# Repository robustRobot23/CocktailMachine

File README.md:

# CocktailMachine
Check the project Wiki for more information
Currently working on a cocktail machine to pour a shot of liquor, and pump in up to 4 mixers.
Machine contains:
  - 1 Stepper motor
  - 1 A4998 Stepper driver
  - 4 12V DC diagrpham pumps
  - 1 24 LED Neopixel ring
  - 1 Loadcell and HX711 breakout board
  - PCB V1
  - 1 OLED Screen
  - 2 rotary encoder dials and pushbuttons
  
**Code still not fully to working.** 
Currently creating the code structure:
  Machine class
  Cocktail class
  Pump Class

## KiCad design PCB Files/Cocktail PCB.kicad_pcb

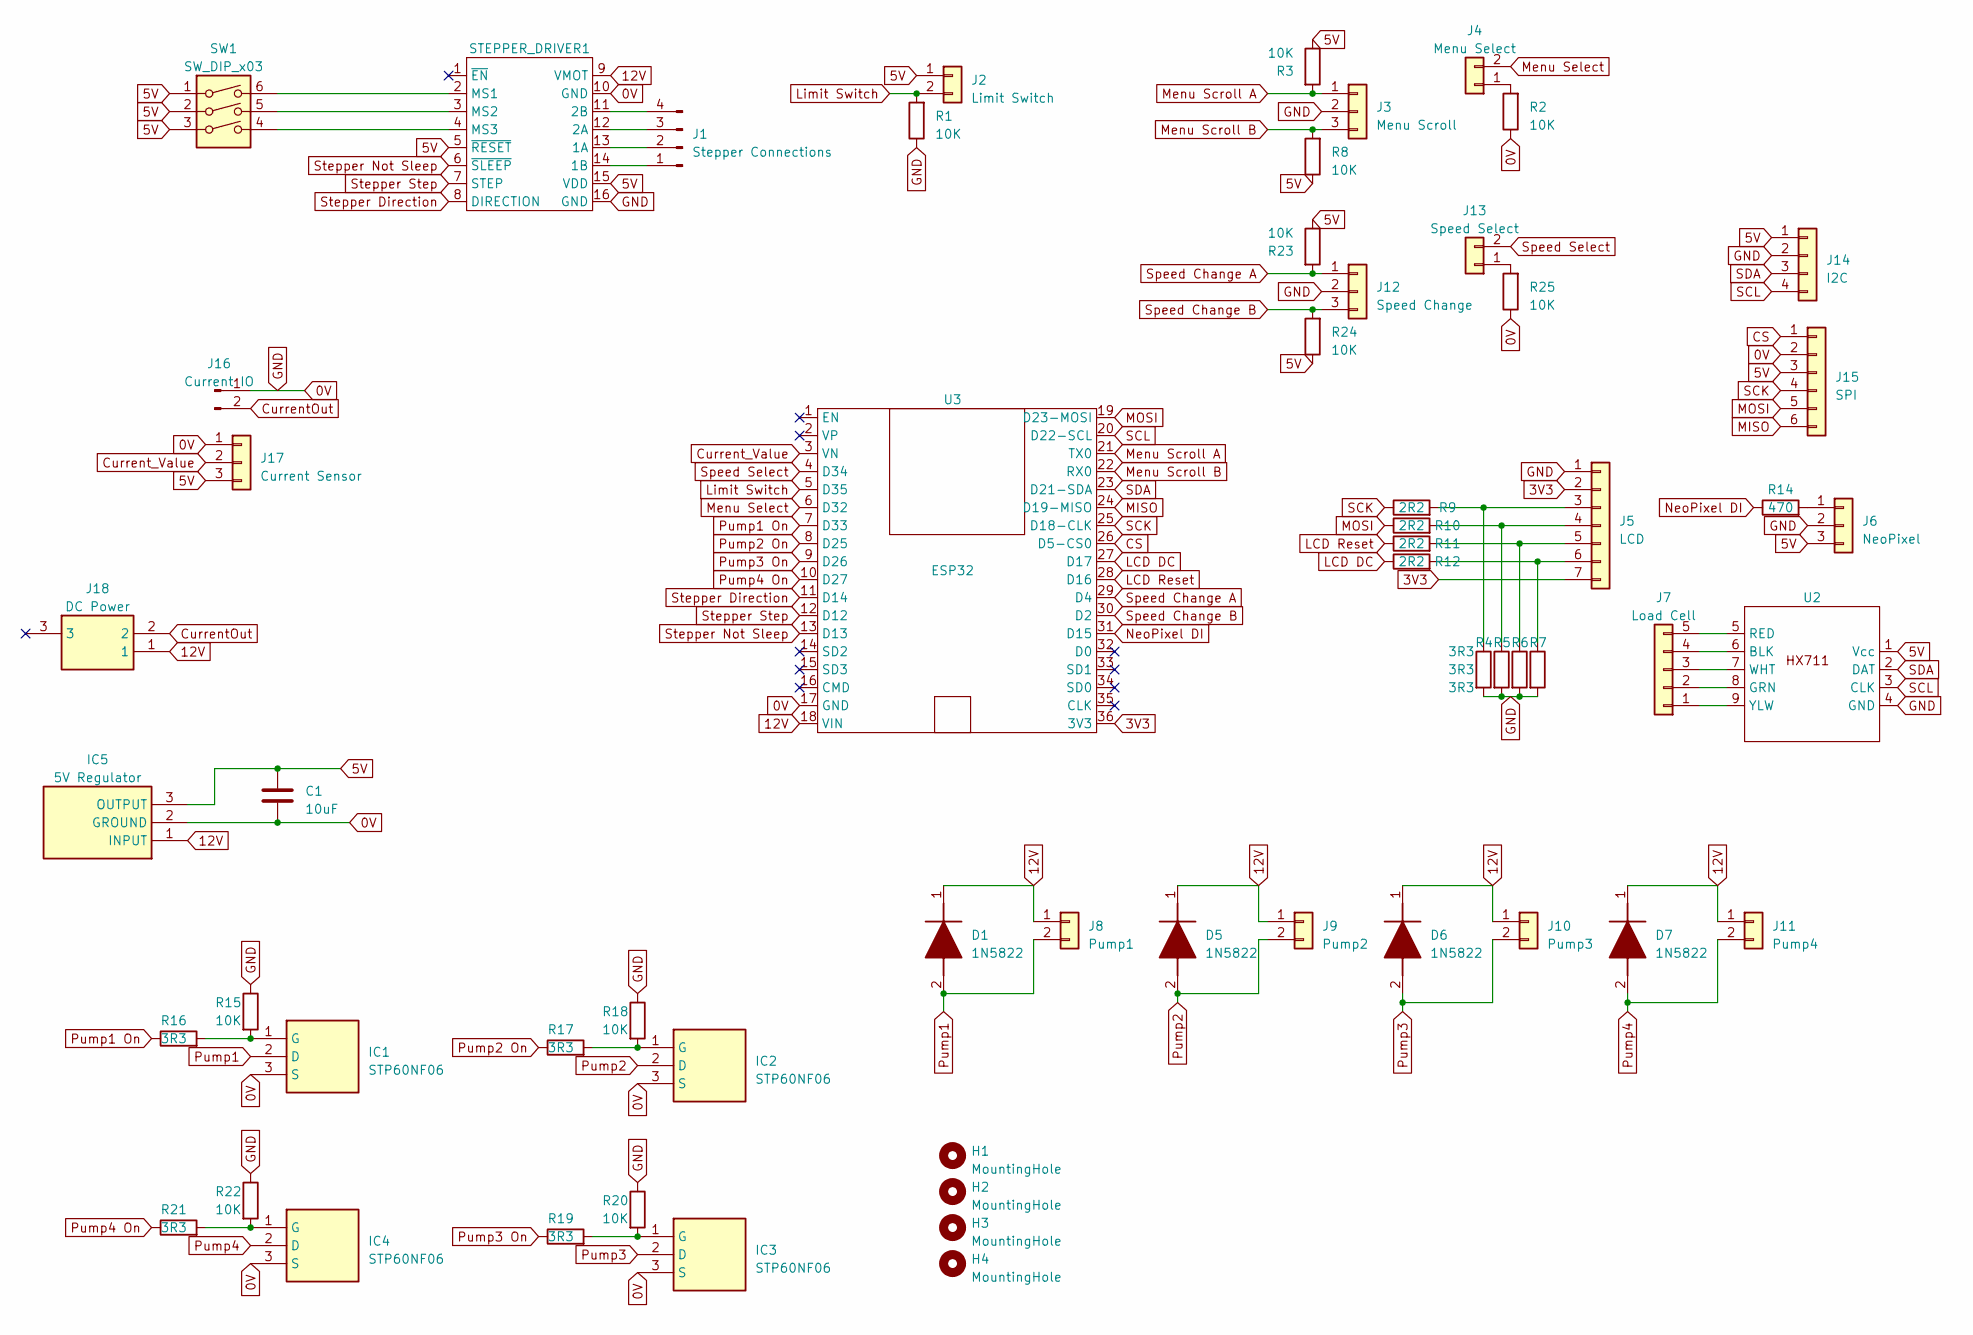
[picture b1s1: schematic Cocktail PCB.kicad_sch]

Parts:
C1: 10uF; CP_Radial_D5.0mm_P2.50mm
D1, D5, D6, D7: 1N5822; D_DO-41_SOD81_P10.16mm_Horizontal; Manufacturer_Part_Number 1N5822; Mouser Part Number 512-1N5822
H1, H2, H3, H4: MountingHole; MountingHole_3.5mm_Pad
IC1, IC2, IC3, IC4: STP60NF06; TO270P460X1020X2008-3P; Manufacturer_Part_Number STP60NF06; Mouser Part Number 511-STP60NF06
IC5: 5V Regulator; TO270P460X1020X2008-3P; Manufacturer_Part_Number LM340T-5.0; Mouser Part Number 926-LM340T-50
J1: Stepper Connections; PinHeader_1x04_P2.54mm_Vertical
J2: Limit Switch; PinHeader_1x02_P2.54mm_Vertical
J3: Menu Scroll; PinHeader_1x03_P2.54mm_Vertical
J4: Menu Select; PinHeader_1x02_P2.54mm_Vertical
J5: LCD; PinHeader_1x07_P2.54mm_Vertical
J6: NeoPixel; PinHeader_1x03_P2.54mm_Vertical
J7: Load Cell; PinHeader_1x05_P2.54mm_Vertical
J8: Pump1; PinHeader_1x02_P2.54mm_Vertical
J9: Pump2; PinHeader_1x02_P2.54mm_Vertical
J10: Pump3; PinHeader_1x02_P2.54mm_Vertical
J11: Pump4; PinHeader_1x02_P2.54mm_Vertical
J12: Speed Change; PinHeader_1x03_P2.54mm_Vertical
J13: Speed Select; PinHeader_1x02_P2.54mm_Vertical
J14: I2C; PinHeader_1x04_P2.54mm_Vertical
J15: SPI; PinHeader_1x06_P2.54mm_Vertical
J16: Current IO; PinHeader_1x02_P2.54mm_Vertical
J17: Current Sensor; PinHeader_1x03_P2.54mm_Vertical
J18: DC Power; DC Jack; Manufacturer_Part_Number PJ-102AH
R1, R2, R3, R8, R15, R18, R20, R22, R23, R24, R25: 10K; R_0805_2012Metric_Pad1.20x1.40mm_HandSolder
R4, R5, R6, R7, R16, R17, R19, R21: 3R3; R_0805_2012Metric_Pad1.20x1.40mm_HandSolder
R9, R10, R11, R12: 2R2; R_0805_2012Metric_Pad1.20x1.40mm_HandSolder
R14: 470; R_0805_2012Metric_Pad1.20x1.40mm_HandSolder
STEPPER_DRIVER1: A4988
SW1: SW_DIP_x03; DIL Switch
U2: HX711
U3: ESP32; DOIT ESP32 DEVKIT

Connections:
0V: C1.2, IC1.3 (S), IC2.3 (S), IC3.3 (S), IC4.3 (S), IC5.2 (GROUND), J3.2, J5.1, J6.2, J12.2, J14.2, J15.2, J16.1, J17.1, R1.1, R2.1, R4.2, R5.2, R6.2, R7.2, R15.1, R18.1, R20.1, R22.1, R25.1, STEPPER_DRIVER1.10 (GND), STEPPER_DRIVER1.16 (GND), U2.4 (GND), U3.17 (GND)
3V3: J5.2, J5.7, U3.36 (3V3)
5V: C1.1, IC5.3 (OUTPUT), J2.1, J6.3, J14.1, J15.3, J17.3, R3.1, R8.1, R23.1, R24.1, STEPPER_DRIVER1.5 (~RESET), STEPPER_DRIVER1.15 (VDD), SW1.1, SW1.2, SW1.3, U2.1 (Vcc)
12V: D1.1 (K), D5.1 (K), D6.1 (K), D7.1 (K), IC5.1 (INPUT), J8.1, J9.1, J10.1, J11.1, J18.1, STEPPER_DRIVER1.9 (VMOT), U3.18 (VIN)
CS: J15.1, U3.26 (D5-CS0)
CurrentOut: J16.2, J18.2
Current_Value: J17.2, U3.3 (VN)
LCD DC: R12.1, U3.27 (D17)
LCD Reset: R11.1, U3.28 (D16)
Limit Switch: J2.2, R1.2, U3.5 (D35)
MISO: J15.6, U3.24 (D19-MISO)
MOSI: J15.5, R10.1, U3.19 (D23-MOSI)
Menu Scroll A: J3.1, R3.2, U3.21 (TX0)
Menu Scroll B: J3.3, R8.2, U3.22 (RX0)
Menu Select: J4.2, U3.6 (D32)
NeoPixel DI: R14.1, U3.31 (D15)
unnamed: IC1.1 (G), R15.2, R16.2
unnamed: IC2.1 (G), R17.2, R18.2
unnamed: IC3.1 (G), R19.2, R20.2
unnamed: IC4.1 (G), R21.2, R22.2
unnamed: J1.1, STEPPER_DRIVER1.14 (1B)
unnamed: J1.2, STEPPER_DRIVER1.13 (1A)
unnamed: J1.3, STEPPER_DRIVER1.12 (2A)
unnamed: J1.4, STEPPER_DRIVER1.11 (2B)
unnamed: J4.1, R2.2
unnamed: J5.3, R4.1, R9.2
unnamed: J5.4, R5.1, R10.2
unnamed: J5.5, R6.1, R11.2
unnamed: J5.6, R7.1, R12.2
unnamed: J6.1, R14.2
unnamed: J7.1, U2.9 (YLW)
unnamed: J7.2, U2.8 (GRN)
unnamed: J7.3, U2.7 (WHT)
unnamed: J7.4, U2.6 (BLK)
unnamed: J7.5, U2.5 (RED)
unnamed: J13.1, R25.2
unnamed: STEPPER_DRIVER1.2 (MS1), SW1.6
unnamed: STEPPER_DRIVER1.3 (MS2), SW1.5
unnamed: STEPPER_DRIVER1.4 (MS3), SW1.4
Pump1: D1.2 (A), IC1.2 (D), J8.2
Pump1 On: R16.1, U3.7 (D33)
Pump2: D5.2 (A), IC2.2 (D), J9.2
Pump2 On: R17.1, U3.8 (D25)
Pump3: D6.2 (A), IC3.2 (D), J10.2
Pump3 On: R19.1, U3.9 (D26)
Pump4: D7.2 (A), IC4.2 (D), J11.2
Pump4 On: R21.1, U3.10 (D27)
SCK: J15.4, R9.1, U3.25 (D18-CLK)
SCL: J14.4, U2.3 (CLK), U3.20 (D22-SCL)
SDA: J14.3, U2.2 (DAT), U3.23 (D21-SDA)
Speed Change A: J12.1, R23.2, U3.29 (D4)
Speed Change B: J12.3, R24.2, U3.30 (D2)
Speed Select: J13.2, U3.4 (D34)
Stepper Direction: STEPPER_DRIVER1.8 (DIRECTION), U3.11 (D14)
Stepper Not Sleep: STEPPER_DRIVER1.6 (~SLEEP), U3.13 (D13)
Stepper Step: STEPPER_DRIVER1.7 (STEP), U3.12 (D12)

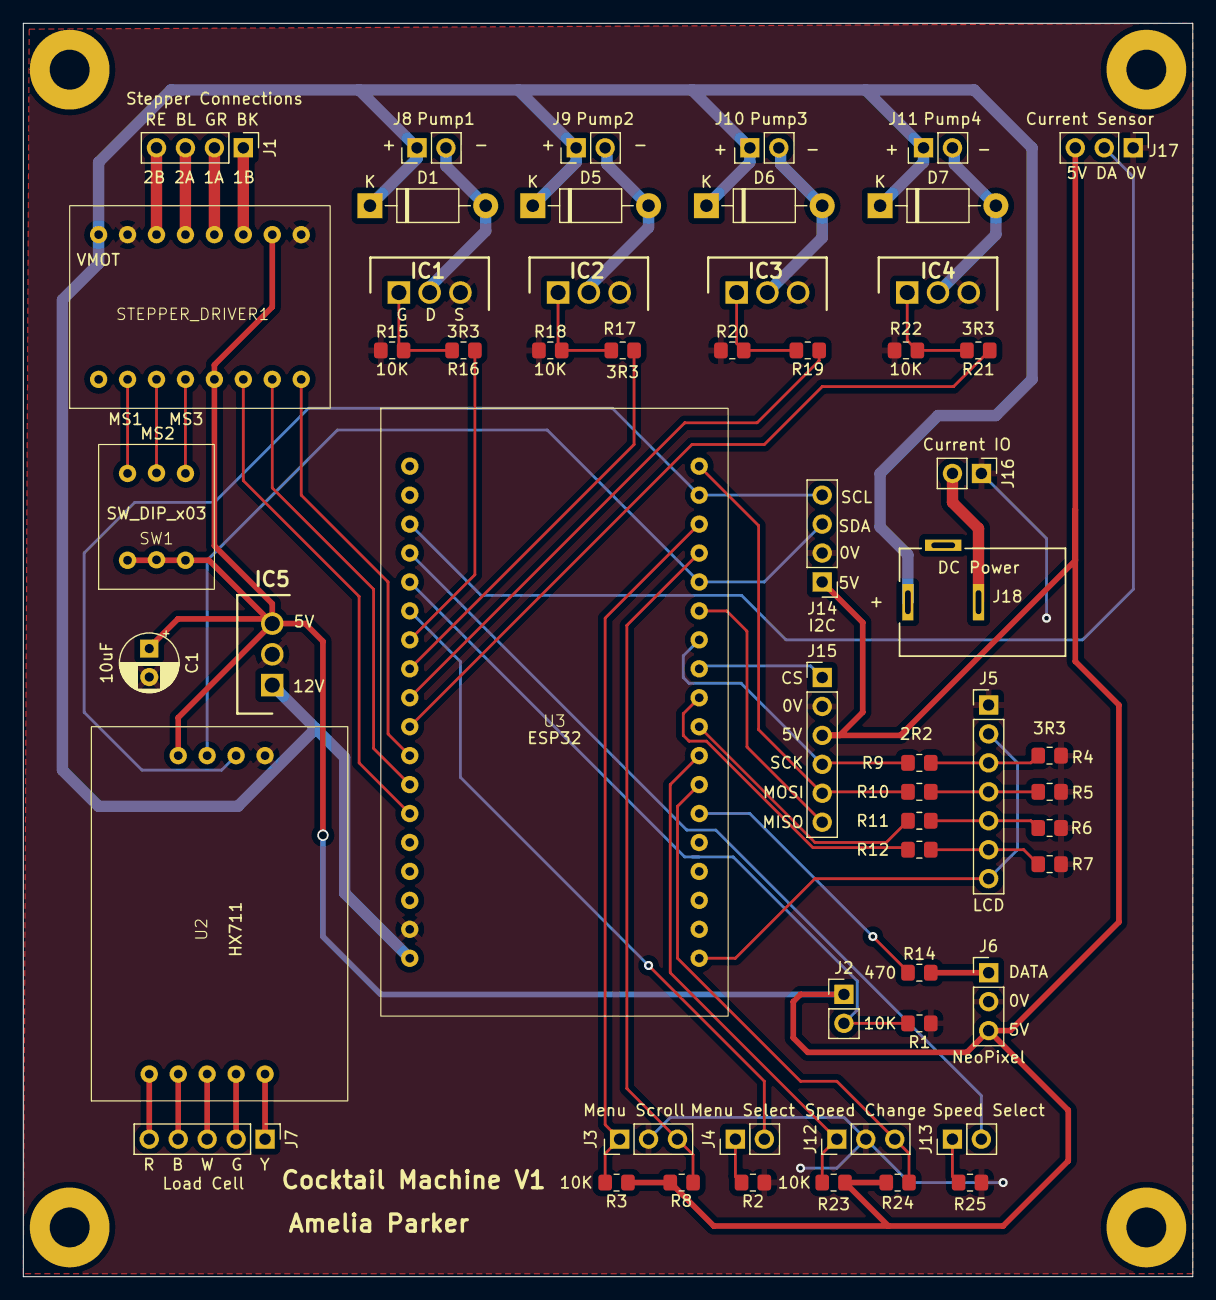
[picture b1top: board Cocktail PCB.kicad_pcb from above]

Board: 2 copper layers, 102.6 x 110.0 mm, 60 parts (0 on the bottom side), 56 nets.

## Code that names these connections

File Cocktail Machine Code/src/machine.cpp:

#include "machine.hpp" 

Machine::Machine() {
    Serial.println("Machine Object Created");
    initCocktails();
}

/// @brief Initialises all cocktails
void Machine::initCocktails() {
    Cocktail GnT(Gin, ONE_SHOT, Tonic, THREE_QUARTERS_CUP, None, 0, None, 0, None, 0);
    Cocktail GinLemonade(Gin, TWO_SHOTS, Lemonade, HALF_CUP, None, 0, None, 0, None, 0);
    Cocktail RumCoke(Rum, ONE_SHOT, Coke, THREE_QUARTERS_CUP, None, 0, None, 0, None, 0);

    allCocktails[0] = GnT;
    allCocktails[1] = GinLemonade;
    allCocktails[2] = RumCoke;
}

bool Machine::cocktailAvailable(int i) {
    Cocktail *cocktail = availableCocktails[i];
    bool available;
    for (int m = 0; m < 4; m++){
        available = false;
        for (int possibleMixer = 0; possibleMixer < NUMBER_MIXERS; possibleMixer++)
            if (cocktail->mixers[m] == possibleMixer) {
                available = true;
                break;
            }
        if (!available) {
            break;
        }
    }
    return available;
}

int Machine::findAvailable() {

    Cocktail *CurrentCocktail;
    int numAvailableCocktails = 0;
    for (int i = 0; i < TOTAL_NUMBER_COCKTAILS; i++) {
        CurrentCocktail = &allCocktails[i];
        if (cocktailAvailable(i)){
            availableCocktails[numAvailableCocktails++] = CurrentCocktail;
        }
    }
    return numAvailableCocktails;
}

void Machine::initAll() {
    Pumps pump1(PUMP_PIN_1);
    Pumps pump2(PUMP_PIN_2);
    Pumps pump3(PUMP_PIN_3);
    Pumps pump4(PUMP_PIN_4);
    pumps[0] = &pump1;
    pumps[1] = &pump2;
    pumps[2] = &pump3;
    pumps[3] = &pump4;
}

void Machine::requestMixer(int i) {
    //display that we need mixer #i??
    //
}


void Machine::run() {
    switch (state) {
        case initIngredients:
            //Definitely want to improve this state
            // receive user input for ingredients
            for (int i = 0; i < 4; i++) {
                if (!pumps[i]->mixer) {
                    //This line might change or be removed by an interupt
                    requestMixer(i);
                    break;
                }
            }

            if (!liquor) {
                //request liquor
            } else { //all has been initialised
                //create list of available pumps
                // if (completeSelection()) {
                //     
                //     state = displayMenu;
                // }
            }

            break;

        case displayMenu:

        //psuedocode ish
            // OLED.display(availableCocktails[i])

            // if (cocktailSelected) {
            //      currentCocktail = availableCocktails[i];
            //      state = makeDrink;
            // }
            break;

        case makeDrink:
            if (!stepperFinished) {
                //run stepper for x amount of shots
            } else if (!pumpsFinished) {
                pumpsFinished = true; //unless proven otherwise
                for (int i = 0; i < 4; i++) {
                    if (!pumps[i]->finished) {
                        pumpsFinished = false;
                        pumps[i]->pumpRun();
                    }
                }
            } else {
                state = enjoy;
            }
            break;
        // case enjoy:
        //     //display "enjoy drink"
        //     //play with neopixel
        //     //Check loadcell for cup removal
        //     break;

    }
}

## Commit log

2023-06-09 First version of PCB. Contains a few errors, mainly not realising esp32 peripherals work on 3.3V logic
2023-06-10 Test commit
2023-06-10 Code for cocktail machine
2023-06-10 Cocktail class header file
2023-06-10 Blank main
2023-06-10 Readable mixer list
2023-06-10 Compiles
2023-06-10 Added messy pump code
2023-06-10 Pumps
2023-06-10 Pumps?
2023-06-10 Adding peripheral files
2023-06-10 Added pump class to turn pumps on and off. Each pump will need to be told the mL of the selected cocktail. The pumpRun method currently needs to be called frequently when pouring.
2023-06-10 Added peripheral modules
2023-06-10 Made a CocktailMachine class that holds info. This includes machine state, and progress of drink making. Pumps have own class. Cocktail is now seperate classs. Kernal can be absorbed into machine cla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
2023-06-10 Delete state.hpp
    State has been moved into machine.hpp
2023-06-10 Delete kernal.hpp
    Run function moved into machine module
2023-06-10 Delete kernal.cpp
    Run moved into machine
2023-06-11 Added run function
2023-06-11 Won't compile
2023-06-11 Constructors have overload supposedly
2023-06-11 Moved files to lib folder
2023-06-11 Absolutely do not understand how C++ constructors work.
2023-06-11 Dependency files
2023-06-11 Compiles happily
2023-06-11 Adding Blynk functionality temporarlily
2023-06-11 Reinstate gitignore
2023-06-12 Create LICENSE
2023-06-12 Uncomplete progress
2023-06-12 Moved PCB files to new folder
2023-06-12 Moved folders around
2023-06-12 Updating folders
2023-06-18 'multipile definitions of 'Blynk''
2023-06-18 Compile ok
2023-06-19 Moved Blynk includes into cpp file. Compiles now
2023-06-19 Attempting to get blynk FSM working. Having trouble with selecting the mixers.
2023-06-19 No new functionality
2023-06-19 Update neopixel colour when state changes. Added LIME colour
2023-06-19 Moved pump1 etc objects to static memory
2023-06-19 Moved pump1 etc objects inside pumpsInit()
2023-06-19 Initialising ingredients works mostly. ESP32 restarting when entering displayMenu state. Likely an empty availableCocktails array
2023-06-26 FSM works, other than resetDisplay() being called. Repeatedly
2023-06-28 tidied up the code
2023-07-06 Added helper functions: tp reduce the size of other functions
